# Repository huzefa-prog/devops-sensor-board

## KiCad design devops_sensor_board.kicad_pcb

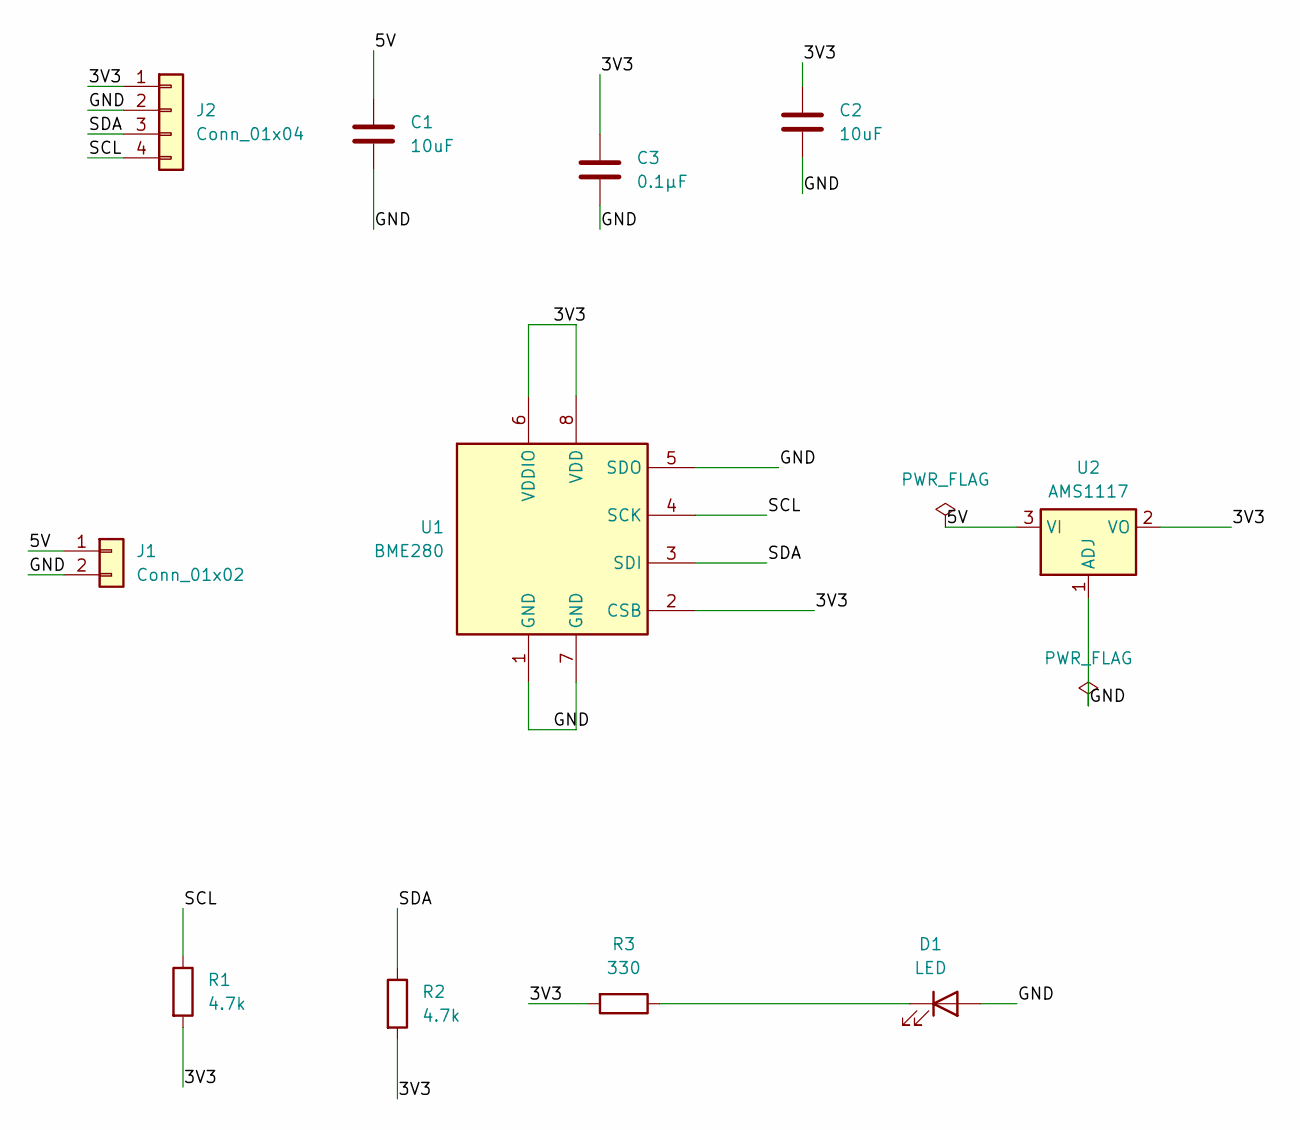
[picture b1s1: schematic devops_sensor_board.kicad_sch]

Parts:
C1, C2: 10uF; C_0805_2012Metric_Pad1.18x1.45mm_HandSolder
C3: 0.1µF; C_0805_2012Metric_Pad1.18x1.45mm_HandSolder
D1: LED; LED_0805_2012Metric_Pad1.15x1.40mm_HandSolder
J1: Conn_01x02; PinHeader_1x02_P2.54mm_Vertical
J2: Conn_01x04; FanPinHeader_1x04_P2.54mm_Vertical
R1, R2: 4.7k; R_0805_2012Metric_Pad1.20x1.40mm_HandSolder
R3: 330; R_0805_2012Metric_Pad1.20x1.40mm_HandSolder
U1: BME280; Bosch_LGA-8_2.5x2.5mm_P0.65mm_ClockwisePinNumbering
U2: AMS1117; SOT-223-3_TabPin2

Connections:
/3V3: C2.1, C3.1, J2.1, R1.2, R2.2, R3.2, U1.2 (CSB), U1.6 (VDDIO), U1.8 (VDD), U2.2 (VO)
/5V: C1.1, J1.1, U2.3 (VI)
/GND: C1.2, C2.2, C3.2, D1.2 (A), J1.2, J2.2, U1.1 (GND), U1.5 (SDO), U1.7 (GND), U2.1 (ADJ)
/SCL: J2.4, R1.1, U1.4 (SCK)
/SDA: J2.3, R2.1, U1.3 (SDI)
unnamed: D1.1 (K), R3.1

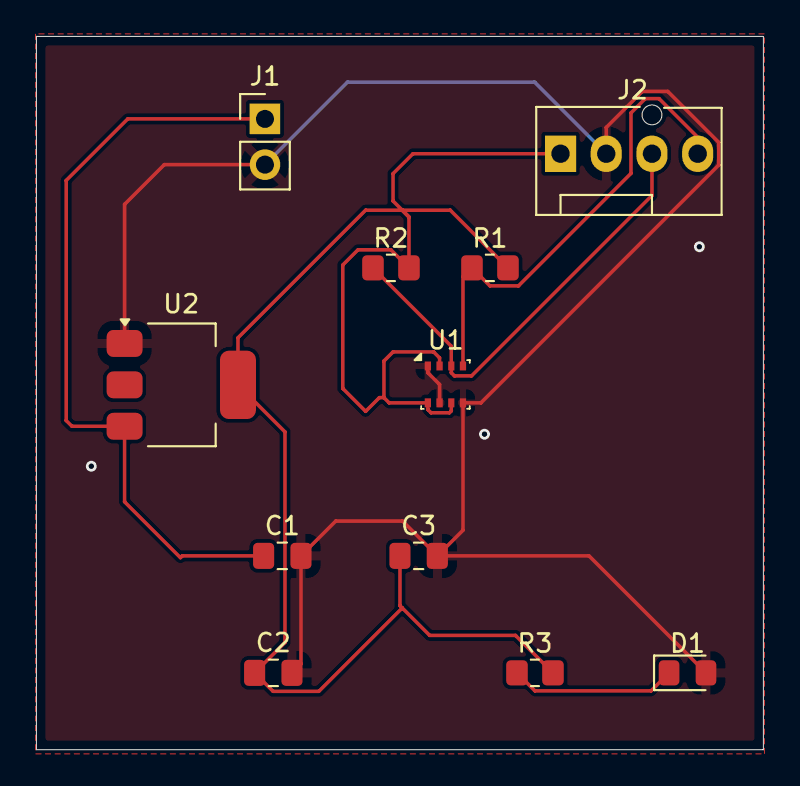
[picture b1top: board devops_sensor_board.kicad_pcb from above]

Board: 2 copper layers, 40.4 x 39.6 mm, 11 parts (0 on the bottom side), 6 nets.

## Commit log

2026-03-23 My PCB project
2026-03-23 Added gitignore
2026-03-23 Fixed gitignore
2026-03-23 Added pipeline
2026-03-23 Updated pipeline with outputs
2026-03-23 trigger pipeline
2026-03-23 Fixed pipeline
